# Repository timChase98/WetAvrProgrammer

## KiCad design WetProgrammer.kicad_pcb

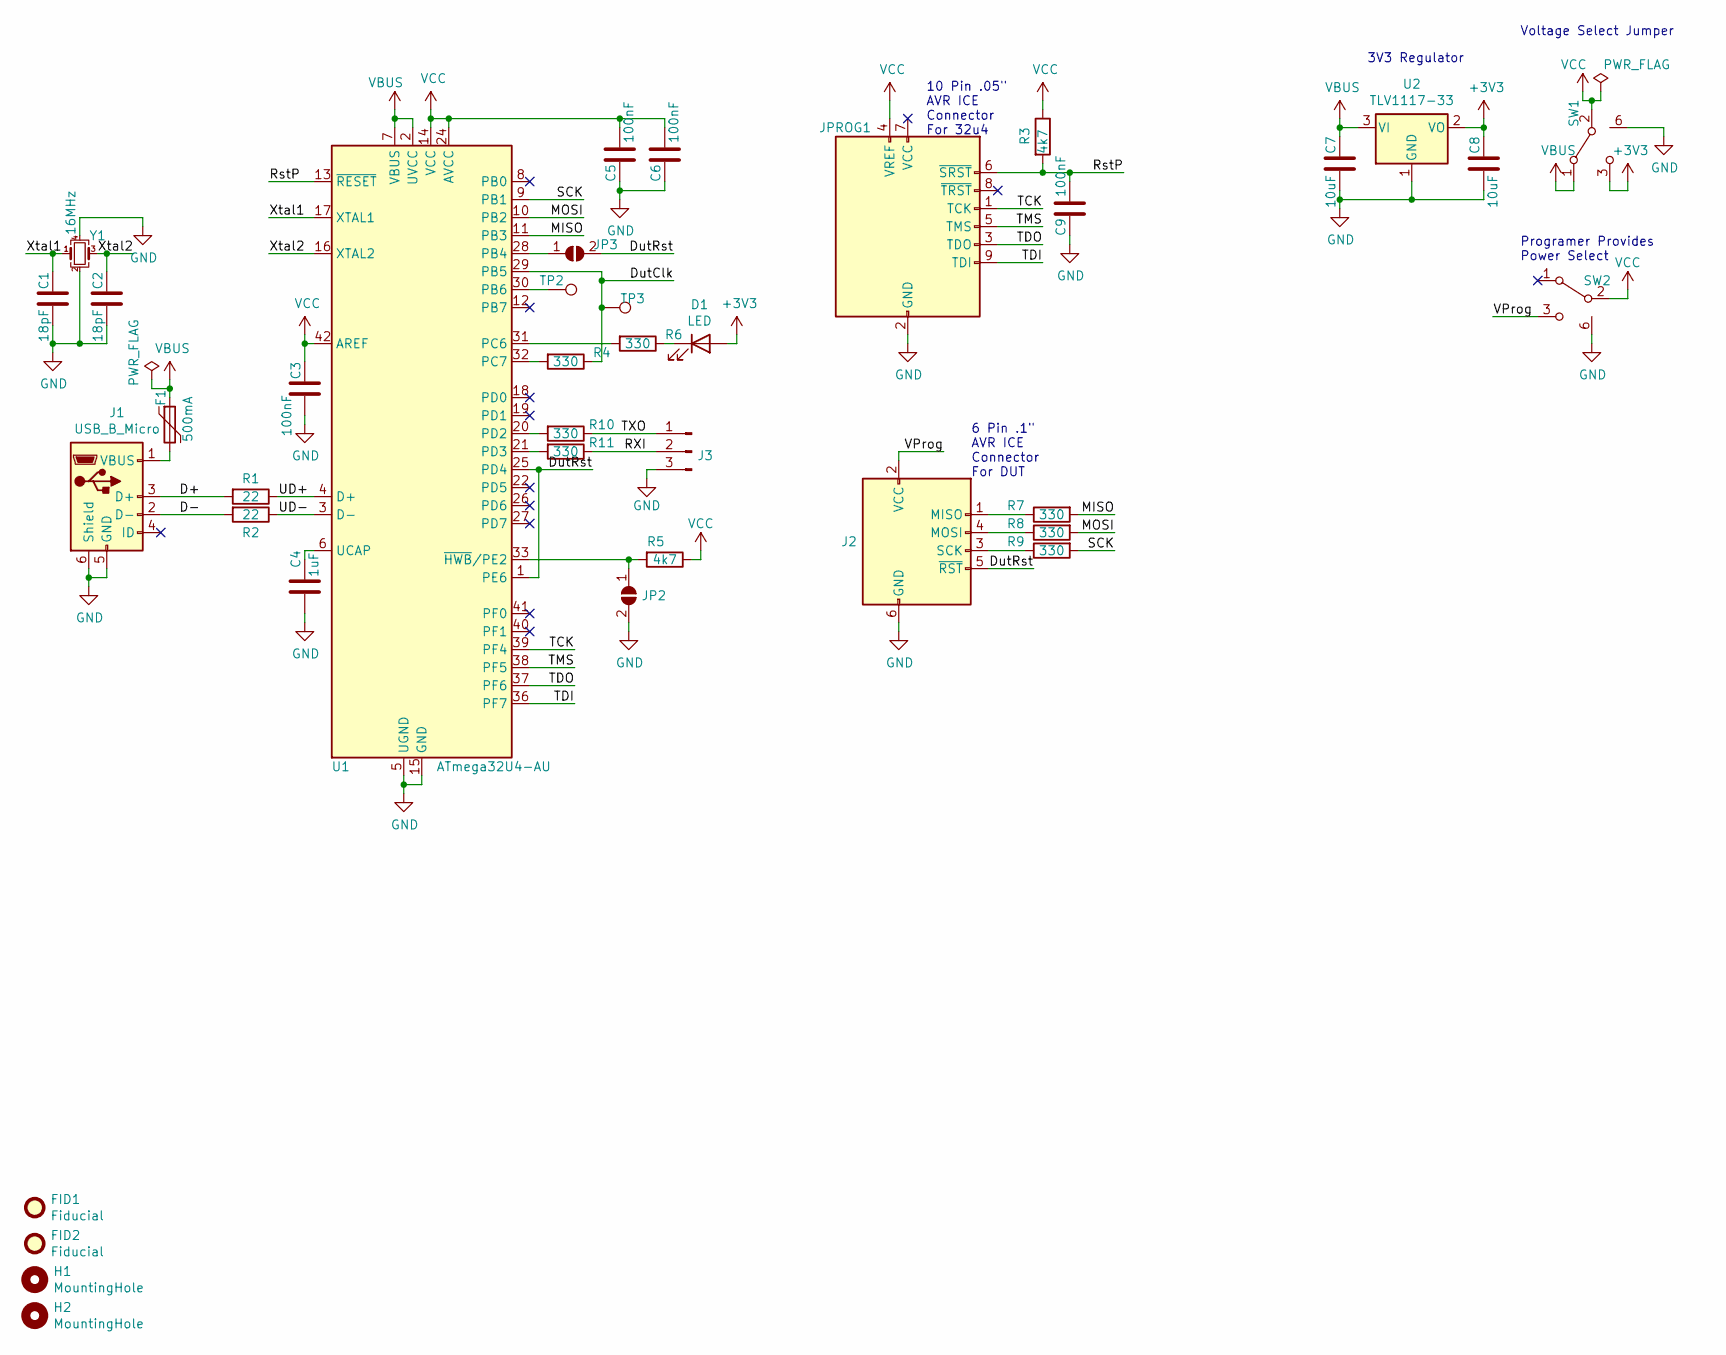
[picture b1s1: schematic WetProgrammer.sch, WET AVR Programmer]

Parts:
C1, C2: 18pF; C_0805_2012Metric
C3, C5, C6, C9: 100nF; C_0805_2012Metric
C4: 1uF; C_0805_2012Metric
C7, C8: 10uF; C_0805_2012Metric
D1: LED; LED_0805_2012Metric
F1: 500mA; Fuse_0805_2012Metric_Castellated
FID1, FID2: Fiducial; Fiducial_1mm_Mask2mm
H1, H2: MountingHole; MountingHole_3.2mm_M3
J1: USB_B_Micro; usbMicro
J2: AVR-ISP-6; PinHeader_2x03_P2.54mm_Vertical
J3: Conn_01x03_Male; PinHeader_1x03_P2.54mm_Vertical
JP2, JP3: SolderJumper_2_Open; SolderJumper-2_P1.3mm_Open_Pad1.0x1.5mm
JPROG1: AVR-ISP-10; PinHeader_2x05_P1.27mm_Vertical
R1, R2: 22; R_0805_2012Metric
R3, R5: 4k7; R_0805_2012Metric
R4, R6, R7, R8, R9, R10, R11: 330; R_0805_2012Metric
SW1, SW2: SW_SPDT; 388Switch
TP2, TP3: TestPoint; TestPoint_Pad_D1.5mm
U1: ATmega32U4-AU; TQFP-44_10x10mm_P0.8mm
U2: TLV1117-33; SOT-223-3_TabPin2
Y1: 16MHz; Crystal_SMD_3225-4Pin_3.2x2.5mm

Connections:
+3V3: C8.1, D1.2 (A), SW1.3 (C), U2.2 (VO)
/D+: J1.3 (D+), R1.2
/D-: J1.2 (D-), R2.2
/DutClk: R4.1, TP3.1, U1.29 (PB5)
/DutRst: J2.5 (~RST), JP3.2 (B), U1.1 (PE6), U1.25 (PD4)
/MISO: R7.2, U1.11 (PB3)
/MOSI: R8.2, U1.10 (PB2)
/RXI: J3.2, R11.1
/RstP: C9.2, JPROG1.6 (~SRST), R3.2, U1.13 (~RESET)
/SCK: R9.2, U1.9 (PB1)
/TCK: JPROG1.1 (TCK), U1.39 (PF4)
/TDI: JPROG1.9 (TDI), U1.36 (PF7)
/TDO: JPROG1.3 (TDO), U1.37 (PF6)
/TMS: JPROG1.5 (TMS), U1.38 (PF5)
/TXO: J3.1, R10.1
/UD+: R1.1, U1.4 (D+)
/UD-: R2.1, U1.3 (D-)
/VProg: J2.2 (VCC), SW2.3 (C)
/Xtal1: C1.2, U1.17 (XTAL1), Y1.1
/Xtal2: C2.2, U1.16 (XTAL2), Y1.3
GND: C1.1, C2.1, C3.1, C4.2, C5.1, C6.1, C7.2, C8.2, C9.1, J1.5 (GND), J1.6 (Shield), J2.6 (GND), J3.3, JP2.2 (B), JPROG1.2 (GND), JPROG1.10 (GND), SW1.6 (sheild), SW2.6 (sheild), U1.5 (UGND), U1.15 (GND), U1.23 (GND), U1.35 (GND), U1.43 (GND), U2.1 (GND), Y1.2, Y1.4
unnamed: C4.1, U1.6 (UCAP)
unnamed: D1.1 (K), R6.1
unnamed: F1.2, J1.1 (VBUS)
unnamed: J2.1 (MISO), R7.1
unnamed: J2.3 (SCK), R9.1
unnamed: J2.4 (MOSI), R8.1
unnamed: JP2.1 (A), R5.2, U1.33 (~HWB~/PE2)
unnamed: JP3.1 (A), U1.28 (PB4)
unnamed: R4.2, U1.32 (PC7)
unnamed: R6.2, U1.31 (PC6)
unnamed: R10.2, U1.20 (PD2)
unnamed: R11.2, U1.21 (PD3)
unnamed: TP2.1, U1.30 (PB6)
VBUS: C7.1, F1.1, SW1.1 (A), U1.2 (UVCC), U1.7 (VBUS), U2.3 (VI)
VCC: C3.2, C5.2, C6.2, JPROG1.4 (VREF), R3.1, R5.1, SW1.2 (B), SW2.2 (B), U1.14 (VCC), U1.24 (AVCC), U1.34 (VCC), U1.42 (AREF), U1.44 (AVCC)

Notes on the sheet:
Voltage Select Jumper
Programer Provides Power Select
3V3 Regulator
10 Pin .05" AVR ICE Connector For 32u4
6 Pin .1" AVR ICE Connector For DUT

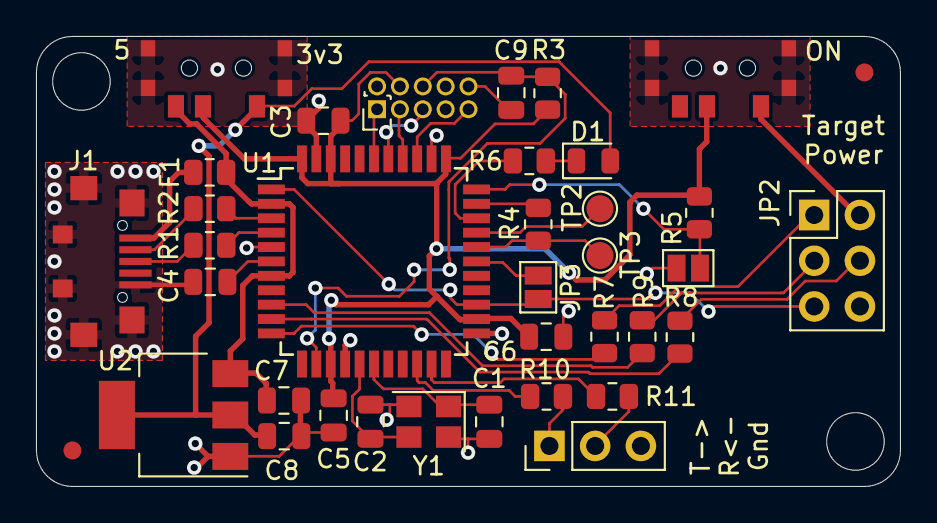
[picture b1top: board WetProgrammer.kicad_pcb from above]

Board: 2 copper layers, 48.0 x 25.0 mm, 40 parts (1 on the bottom side), 36 nets.

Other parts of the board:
wet: Val**; wetLogo

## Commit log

2021-08-31 inital
2021-09-14 push
2021-09-15 Added power flaggs to supress ERC errors
2021-09-15 Rerendered schematic after changes
2021-09-19 Inital Layout
2021-09-19 Rendered Schematic for R1.0
2021-09-21 Changes as requested by Ben
2021-09-21 Connected swtich sheilding to gnd
2021-09-21 Removed unused files
2021-09-22 Changed programmer port to JTAG
2021-09-22 Fixed ground fill on pannel
2021-09-22 at some point i will be good at boards
2021-09-22 at some point i will be good at boards 2
2021-09-24 Testing github actions
2021-09-24 set rev to 1.0
2021-09-25 Updated Renders
2021-09-25 Fixed Switch Labels
